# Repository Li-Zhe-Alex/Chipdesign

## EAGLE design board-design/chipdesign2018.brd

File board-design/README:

Dieser Ordner ist für die Phase-2-Gruppe "Schaltplan & Boardlayout" reserviert

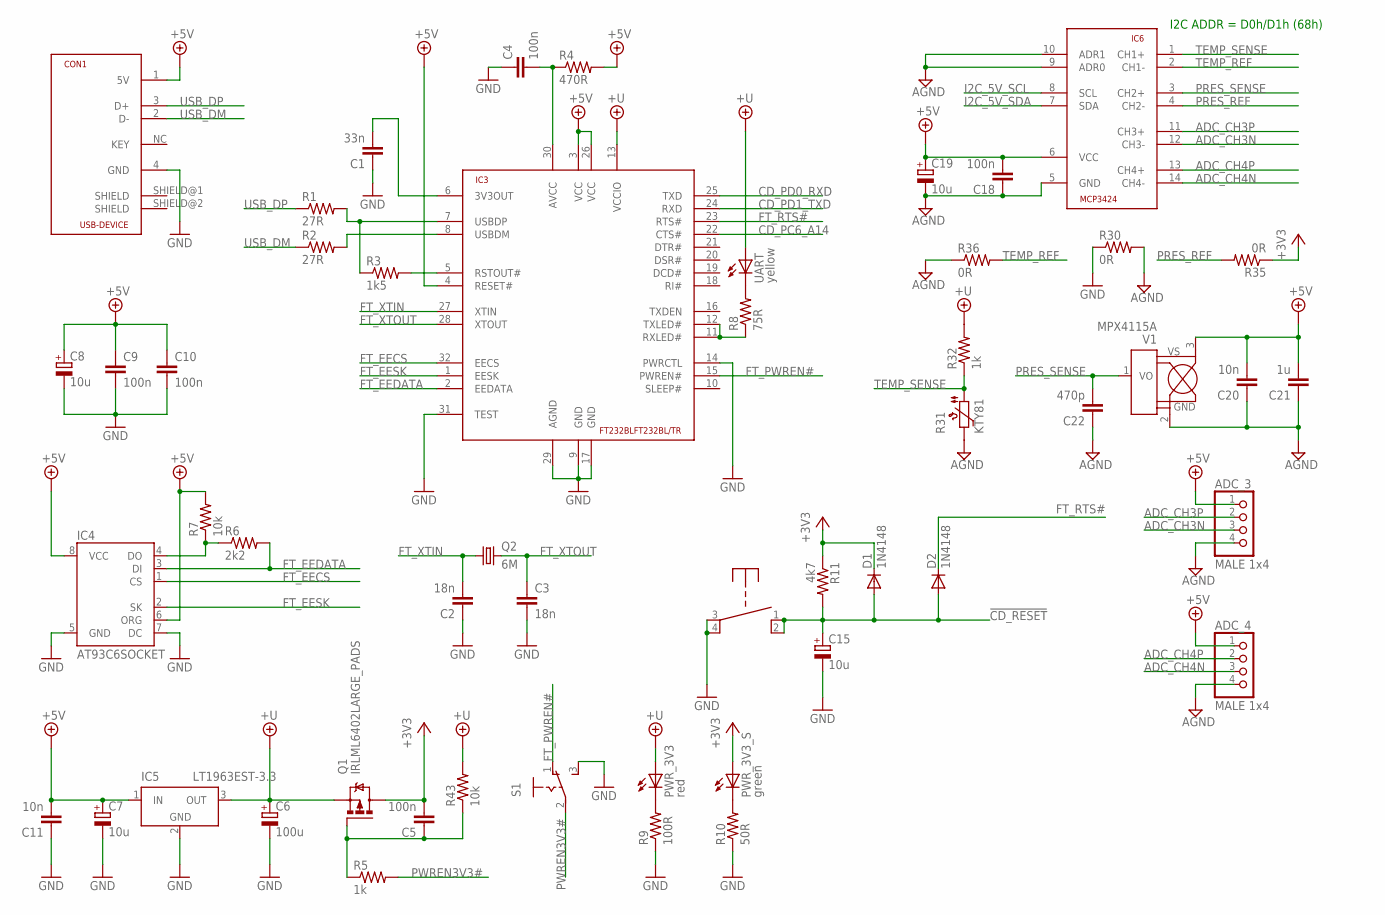
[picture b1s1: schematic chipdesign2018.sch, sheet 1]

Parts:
ADC_3, ADC_4: MALE 1x4; 1X04
C1: 33n; C025-025X050
C2, C3: 18n; C025-025X050
C4, C5, C9, C10, C18: 100n; C025-025X050
C6: 100u; E2,5-6
C7, C8, C15, C19: 10u; E2-5
C11, C20: 10n; C025-025X050
C21: 1u; C025-025X050
C22: 470p; C025-025X050
CON1: USB-DEVICE; USB-B
D1, D2: 1N4148; DO35-7
IC3: FT232BLFT232BL/TR; LQFP-32
IC4: AT93C6SOCKET; SOCKET-08
IC5: LT1963EST-3.3; SOT223
IC6: MCP3424; SO-14
PWR_3V3: red; LED3MM
PWR_3V3_S: green; LED3MM
Q1: IRLML6402LARGE_PADS; SOT23W_INFINEON
Q2: 6M; HC49/S
R1, R2: 27R; 0207/7
R3: 1k5; 0207/7
R4: 470R; 0207/7
R5, R32: 1k; 0207/7
R6: 2k2; 0207/7
R7, R43: 10k; 0207/7
R8: 75R; 0207/7
R9: 100R; 0207/7
R10: 50R; 0207/7
R11: 4k7; 0207/7
R30, R35, R36: 0R; 0207/7
R31: KTY81; SOD70
S1: 255SB
U$1: PHAP3301
UART: yellow; LED3MM
V1: MPX4115A; MPX_CASE867

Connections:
!CD_RESET: C15.+, D1.A, D2.A, R11.2, U$1.1, U$1.2; also elsewhere on the board
+3V3: C5.2, D1.C, PWR_3V3_S.A, Q1.3 (D), R11.1, R35.1; also elsewhere on the board
+5V: ADC_3.1, ADC_4.1, C7.+, C8.+, C9.1, C10.1, C11.2, C18.2, C19.+, C20.2, C21.2, CON1.1 (5V), IC3.3 (VCC), IC3.4 (RESET#), IC3.26 (VCC), IC4.6 (ORG), IC4.8 (VCC), IC5.1 (IN), IC6.6 (VCC), R4.2, R7.2, V1.3 (VS); also elsewhere on the board
+UB: C6.+, IC3.13 (VCCIO), IC5.3 (OUT), PWR_3V3.A, Q1.2 (S), R32.2, R43.2, UART.A
ADC_CH3N: ADC_3.3, IC6.12 (CH3-)
ADC_CH3P: ADC_3.2, IC6.11 (CH3+)
ADC_CH4N: ADC_4.3, IC6.14 (CH4-)
ADC_CH4P: ADC_4.2, IC6.13 (CH4+)
AGND: ADC_3.4, ADC_4.4, C18.1, C19.-, C20.1, C21.1, C22.1, IC6.5 (GND), IC6.9 (ADR0), IC6.10 (ADR1), R30.2, R31.2, R36.1, V1.2 (GND)
CD_PC6_A14: IC3.22 (CTS#); also elsewhere on the board
CD_PD0_RXD: IC3.25 (TXD); also elsewhere on the board
CD_PD1_TXD: IC3.24 (RXD); also elsewhere on the board
EEDO: IC4.4 (DO), R6.1, R7.1
EN3V3#: C5.1, Q1.1 (G), R5.1, R43.1
FT_3V3OUT: C1.2, IC3.6 (3V3OUT)
FT_ACTLED#: IC3.11 (RXLED#), IC3.12 (TXLED#), R8.1
FT_AVCC: C4.2, IC3.30 (AVCC), R4.1
FT_EECS: IC3.32 (EECS), IC4.1 (CS)
FT_EEDATA: IC3.2 (EEDATA), IC4.3 (DI), R6.2
FT_EESK: IC3.1 (EESK), IC4.2 (SK)
FT_PWREN#: IC3.15 (PWREN#), S1.1 (O)
FT_RSTOUT#: IC3.5 (RSTOUT#), R3.2
FT_RTS#: D2.C, IC3.23 (RTS#)
FT_USBDM: IC3.8 (USBDM), R2.2
FT_USBDP: IC3.7 (USBDP), R1.2, R3.1
FT_XTIN: C2.2, IC3.27 (XTIN), Q2.1
FT_XTOUT: C3.1, IC3.28 (XTOUT), Q2.2
GND: C1.1, C2.1, C3.2, C4.1, C6.-, C7.-, C8.-, C9.2, C10.2, C11.1, C15.-, CON1.4 (GND), IC3.9 (GND), IC3.14 (PWRCTL), IC3.17 (GND), IC3.29 (AGND), IC3.31 (TEST), IC4.5 (GND), IC4.7 (DC), IC5.2 (GND), IC5.4 (GND), R9.1, R10.1, R30.1, S1.3 (S), U$1.3, U$1.4; also elsewhere on the board
I2C_5V_SCL: IC6.8 (SCL); also elsewhere on the board
I2C_5V_SDA: IC6.7 (SDA); also elsewhere on the board
unnamed: R8.2, UART.K (C)
unnamed: PWR_3V3.K (C), R9.2
unnamed: PWR_3V3_S.K (C), R10.2
PRES_REF: IC6.4 (CH2-), R35.2
PRES_SENSE: C22.2, IC6.3 (CH2+), V1.1 (VO+)
PWREN3V3#: R5.2, S1.2
TEMP_REF: IC6.2 (CH1-), R36.2
TEMP_SENSE: IC6.1 (CH1+), R31.1, R32.1
USB_DM: CON1.2 (D-), R2.1
USB_DP: CON1.3 (D+), R1.1

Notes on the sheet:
I2C ADDR = D0h/D1h (68h)

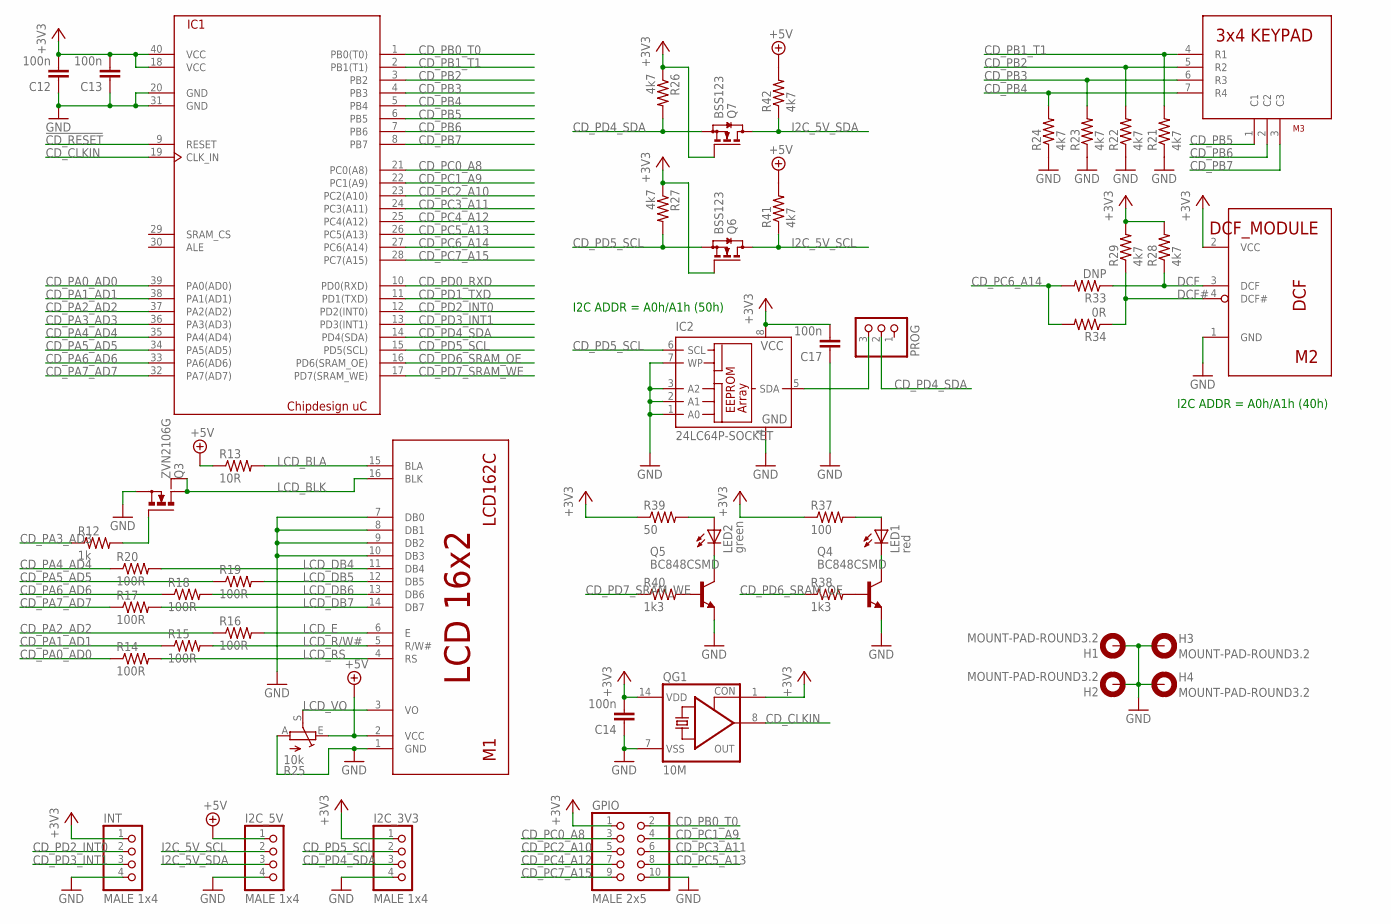
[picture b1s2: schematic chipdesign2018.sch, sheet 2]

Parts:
C12, C13, C14, C17: 100n; C025-025X050
GPIO: MALE 2x5; 2X05
H1, H2, H3, H4: MOUNT-PAD-ROUND3.2; 3,2-PAD
I2C_3V3, I2C_5V: MALE 1x4; 1X04
IC1: Chipdesign uC; FPGA-BOARD-2X20
IC2: 24LC64P-SOCKET; SOCKET-08
INT: MALE 1x4; 1X04
LED1: red; LED3MM
LED2: green; LED3MM
M1: LCD162C
M2: DCF_MODULE
M3: KEYPAD
PROG: PINHD-1X3; 1X03
Q3: ZVN2106G; SOT223
Q4, Q5: BC848CSMD; SOT23
Q6, Q7: BSS123; SOT23
QG1: 10M; SG51
R12: 1k; 0207/7
R13: 10R; 0207/7
R14, R15, R16, R17, R18, R19, R20: 100R; 0207/7
R21, R22, R23, R24, R26, R27, R28, R29, R41, R42: 4k7; 0207/7
R25: 10k; ST6
R33: DNP; 0207/7
R34: 0R; 0207/7
R37: 100; 0207/7
R38, R40: 1k3; 0207/7
R39: 50; 0207/7

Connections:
!CD_RESET: IC1.9 (RESET); also elsewhere on the board
+3V3: C12.2, C13.2, C14.2, C17.2, GPIO.1, I2C_3V3.1, IC1.18 (VCC), IC1.40 (VCC), IC2.8 (VCC), INT.1, M2.2 (VCC), Q6.1 (G), Q7.1 (G), QG1.1 (CON), QG1.14 (VDD), R26.1, R27.1, R28.2, R29.2, R37.1, R39.1; also elsewhere on the board
+5V: I2C_5V.1, M1.2 (VCC), R13.1, R25.E, R41.2, R42.2; also elsewhere on the board
CD_CLKIN: IC1.19 (CLK_IN), QG1.8 (OUT)
CD_PA0_AD0: IC1.39 (PA0(AD0)), R14.1
CD_PA1_AD1: IC1.38 (PA1(AD1)), R15.1
CD_PA2_AD2: IC1.37 (PA2(AD2)), R16.1
CD_PA3_AD3: IC1.36 (PA3(AD3)), R12.1
CD_PA4_AD4: IC1.35 (PA4(AD4)), R20.1
CD_PA5_AD5: IC1.34 (PA5(AD5)), R19.1
CD_PA6_AD6: IC1.33 (PA6(AD6)), R18.1
CD_PA7_AD7: IC1.32 (PA7(AD7)), R17.1
CD_PB0_T0: GPIO.2, IC1.1 (PB0(T0))
CD_PB1_T1: IC1.2 (PB1(T1)), M3.4 (R1), R21.2
CD_PB2: IC1.3 (PB2), M3.5 (R2), R22.2
CD_PB3: IC1.4 (PB3), M3.6 (R3), R23.2
CD_PB4: IC1.5 (PB4), M3.7 (R4), R24.2
CD_PB5: IC1.6 (PB5), M3.1 (C1)
CD_PB6: IC1.7 (PB6), M3.2 (C2)
CD_PB7: IC1.8 (PB7), M3.3 (C3)
CD_PC0_A8: GPIO.3, IC1.21 (PC0(A8))
CD_PC1_A9: GPIO.4, IC1.22 (PC1(A9))
CD_PC2_A10: GPIO.5, IC1.23 (PC2(A10))
CD_PC3_A11: GPIO.6, IC1.24 (PC3(A11))
CD_PC4_A12: GPIO.7, IC1.25 (PC4(A12))
CD_PC5_A13: GPIO.8, IC1.26 (PC5(A13))
CD_PC6_A14: IC1.27 (PC6(A14)), R33.2, R34.2; also elsewhere on the board
CD_PC7_A15: GPIO.9, IC1.28 (PC7(A15))
CD_PD0_RXD: IC1.10 (PD0(RXD)); also elsewhere on the board
CD_PD1_TXD: IC1.11 (PD1(TXD)); also elsewhere on the board
CD_PD2_INT0: IC1.12 (PD2(INT0)), INT.2
CD_PD3_INT1: IC1.13 (PD3(INT1)), INT.3
CD_PD4_SDA: I2C_3V3.3, IC1.14 (PD4(SDA)), PROG.2, Q7.2 (S), R26.2
CD_PD5_SCL: I2C_3V3.2, IC1.15 (PD5(SCL)), IC2.6 (SCL), Q6.2 (S), R27.2
CD_PD6_SRAM_OE: IC1.16 (PD6(SRAM_OE)), R38.1
CD_PD7_SRAM_WE: IC1.17 (PD7(SRAM_WE)), R40.1
DCF: M2.3 (DCF), R28.1, R33.1
DCF#: M2.4 (DCF#), R29.1, R34.1
EEP_SDA: IC2.5 (SDA), PROG.3
GND: C12.1, C13.1, C14.1, C17.1, GPIO.10, H1.B3,2, H2.B3,2, H3.B3,2, H4.B3,2, I2C_3V3.4, I2C_5V.4, IC1.20 (GND), IC1.31 (GND), IC2.1 (A0), IC2.2 (A1), IC2.3 (A2), IC2.4 (GND), IC2.7 (WP), INT.4, M1.1 (GND), M1.7 (DB0), M1.8 (DB1), M1.9 (DB2), M1.10 (DB3), M2.1 (GND), Q3.3 (S), Q4.2 (E), Q5.2 (E), QG1.7 (VSS), R21.1, R22.1, R23.1, R24.1, R25.A; also elsewhere on the board
I2C_5V_SCL: I2C_5V.2, Q6.3 (D), R41.1; also elsewhere on the board
I2C_5V_SDA: I2C_5V.3, Q7.3 (D), R42.1; also elsewhere on the board
LCD_BLA: M1.15 (BLA), R13.2
LCD_BLK: M1.16 (BLK), Q3.2 (D), Q3.4 (D)
LCD_DB4: M1.11 (DB4), R20.2
LCD_DB5: M1.12 (DB5), R19.2
LCD_DB6: M1.13 (DB6), R18.2
LCD_DB7: M1.14 (DB7), R17.2
LCD_E: M1.6 (E), R16.2
LCD_R/W#: M1.5 (R/W#), R15.2
LCD_RS: M1.4 (RS), R14.2
LCD_VO: M1.3 (VO), R25.S
unnamed: Q4.1 (B), R38.2
unnamed: LED1.K (C), Q4.3 (C)
unnamed: LED1.A, R37.2
unnamed: Q5.1 (B), R40.2
unnamed: Q3.1 (G), R12.2
unnamed: LED2.K (C), Q5.3 (C)
unnamed: LED2.A, R39.2

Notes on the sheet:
I2C ADDR = A0h/A1h (50h)
I2C ADDR = A0h/A1h (40h)

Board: 2 copper layers, 103 parts (0 on the bottom side), 90 nets, no tracks yet.

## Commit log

2019-09-19 my project
